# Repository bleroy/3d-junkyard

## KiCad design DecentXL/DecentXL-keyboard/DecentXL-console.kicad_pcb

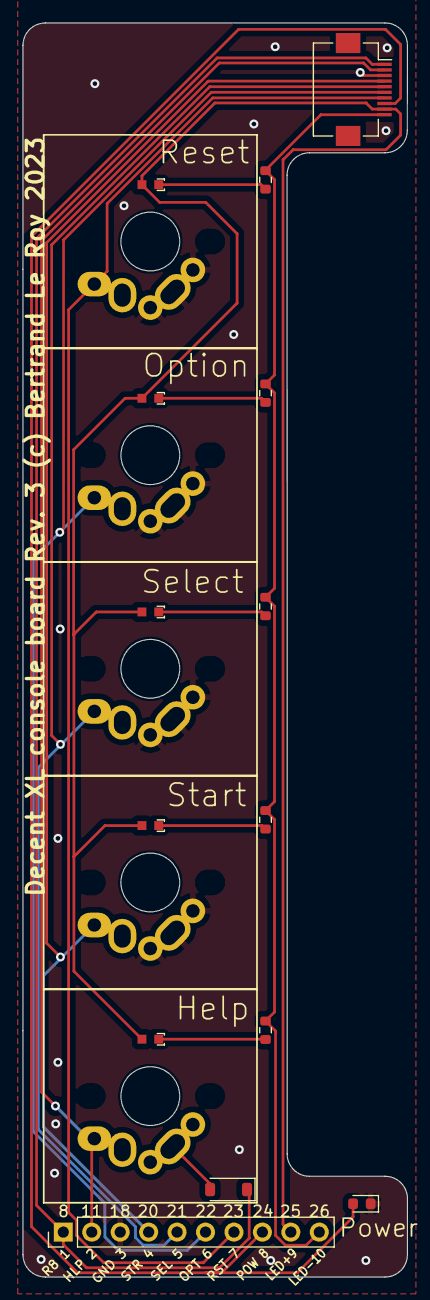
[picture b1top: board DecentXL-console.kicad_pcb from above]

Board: 2 copper layers, 34.3 x 112.0 mm, 14 parts (0 on the bottom side), 16 nets.

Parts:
D0: LED; LED_0603_1608Metric
D11: 1N4148W; D_SOD-123
J4: Conn_01x10; PinHeader_1x10_P2.54mm_Vertical
J5: Conn_01x10; Hirose_FH12-10S-0.5SH_1x10-1MP_P0.50mm_Horizontal
R11, R64, R65, R67, R68: 100; R_0603_1608Metric
SWHlp1: SW_Push_45deg; MX-1-00U-LED
SWOption1: SW_Push_45deg; MX-1-00U-LED
SWReset1: SW_Push_45deg; MX-1-00U-LED
SWSelect1: SW_Push_45deg; MX-1-00U-LED
SWStart1: SW_Push_45deg; MX-1-00U-LED

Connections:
CSL_GND: D0.1 (K), J4.3, J5.3, SWOption1.2, SWReset1.2, SWSelect1.2, SWStart1.2
CSL_HELP: J4.2, J5.2, SWHlp1.1
CSL_LED_GND: J4.10, J5.10, R11.2, R64.2, R65.2, R67.2, R68.2
CSL_OPTION: J4.6, J5.6, SWOption1.1
CSL_PWR_LED: D0.2 (A), J4.8, J5.8
CSL_RESET: J4.7, J5.7, SWReset1.1
CSL_ROW_8: D11.1 (K), J4.1, J5.1
CSL_SELECT: J4.5, J5.5, SWSelect1.1
CSL_START: J4.4, J5.4, SWStart1.1
CSL_VCC_LED: J4.9, J5.9, SWHlp1.4, SWOption1.4, SWReset1.4, SWSelect1.4, SWStart1.4
unnamed: D11.2 (A), SWHlp1.2
unnamed: R11.1, SWHlp1.3
unnamed: R64.1, SWStart1.3
unnamed: R65.1, SWSelect1.3
unnamed: R67.1, SWOption1.3
unnamed: R68.1, SWReset1.3

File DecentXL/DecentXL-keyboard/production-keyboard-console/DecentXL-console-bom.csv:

Designator,Footprint,Quantity,Value,LCSC Part #
D0,0603,1,LED,
D11,D_SOD-123,1,1N4148W,
J5,Hirose_FH12-10S-0.5SH_1x10-1MP_P0.50mm_Horizontal,1,Conn_01x10,
"R11, R64, R65, R67, R68",0603,5,100,
"SWHlp1, SWOption1, SWReset1, SWSelect1, SWStart1",MX-1-00U-LED,5,SW_Push_45deg,

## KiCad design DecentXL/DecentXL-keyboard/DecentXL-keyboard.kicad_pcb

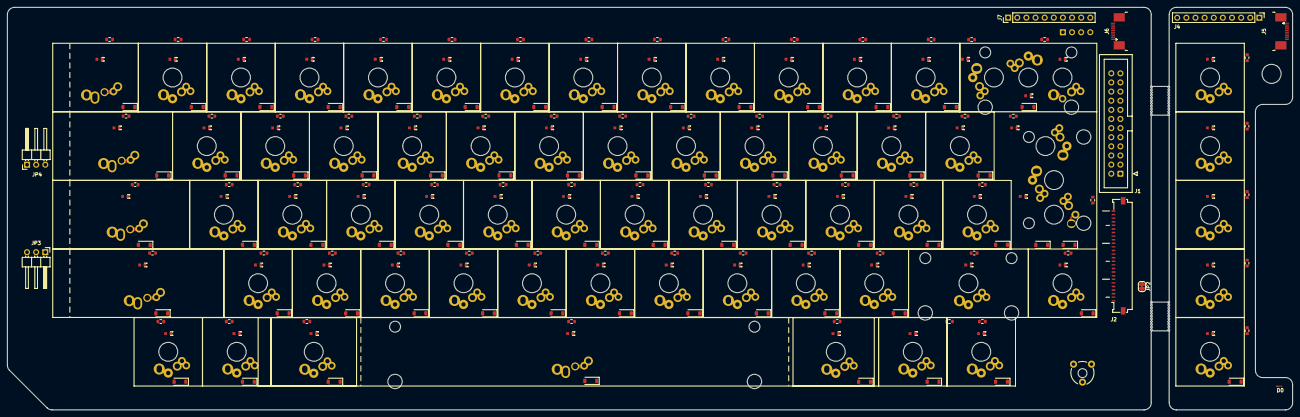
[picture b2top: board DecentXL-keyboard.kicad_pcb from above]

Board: 2 copper layers, 357.6 x 112.0 mm, 212 parts (1 on the bottom side), 168 nets, no tracks yet.

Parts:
D0: LED; LED_0201_0603Metric
D1, D2, D3, D4, D5, D6, D7, D8, D9, D10, D11, D12, D13, D14, D15, D16, D17, D18, D19, D20, D21, D22, D23, D24, D25, D26, D27, D28, D29, D30, D31, D32, D33, D34, D35, D36, D37, D38, D39, D40, D41, D42, D43, D44, D45, D46, D47, D48, D49, D50, D51, D52, D53, D54, D55, D56, D57, D58, D59, D60, D61, D62: 1N4148W; D_SOD-123
J1: Conn_02x12_Odd_Even; IDC-Header_2x12_P2.54mm_Vertical
J2: Conn_01x26; Molex_200528-0260_1x26-1MP_P1.00mm_Horizontal
J3: Conn_01x04; PinHeader_1x04_P2.54mm_Vertical
J4, J7: Conn_01x10; PinHeader_1x10_P2.54mm_Vertical
J5, J6: Conn_01x10; TE_1-1734839-0_1x10-1MP_P0.5mm_Horizontal
JP1: SolderJumper_2_Bridged; Potentiometer_CUI-PTN06-D02CB20
JP2: SolderJumper_2_Bridged; SolderJumper-2_P1.3mm_Bridged_RoundedPad1.0x1.5mm
JP3, JP4: Jumper_3_Bridged12; PinHeader_1x03_P2.54mm_Horizontal
R1, R2, R3, R4, R5, R6, R7, R8, R9, R10, R11, R12, R13, R14, R15, R16, R17, R18, R19, R20, R21, R22, R23, R24, R25, R26, R27, R28, R29, R30, R31, R32, R33, R34, R35, R36, R37, R38, R39, R40, R41, R42, R43, R44, R45, R46, R47, R48, R49, R50, R51, R52, R53, R54, R55, R56, R57, R58, R59, R60, R61, R62, R63, R64, R65, R66, R67, R68: R; R_0603_1608Metric
SW0, SW1, SW2, SW3, SW4, SW5, SW6, SW7, SW8, SW9: SW_Push_45deg; MX-1-00U-LED
SWA1: SW_Push_45deg; MX-1-00U-LED
SWB1: SW_Push_45deg; MX-1-00U-LED
SWBrk1: SW_Push_45deg; MX-1-25U-LED
SWBrk2: SW_Push_45deg; MX-1-00U-LED
SWC1: SW_Push_45deg; MX-1-00U-LED
SWComma1: SW_Push_45deg; MX-1-00U-LED
SWCps1: SW_Push_45deg; MX-1-25U-LED
SWCtl1: SW_Push_45deg; MX-1-25U-LED
SWCtlCaps1: SW_Push_45deg; MX-2-00--1-75-U-LED
SWD1: SW_Push_45deg; MX-1-00U-LED
SWDash1: SW_Push_45deg; MX-1-00U-LED
SWDel1: SWITCH; MX-2-00U-LED
SWDel2: SW_Push_45deg; MX-1-00U-LED
SWE1: SW_Push_45deg; MX-1-00U-LED
SWEqual1: SW_Push_45deg; MX-1-00U-LED
SWEsc1: SW_Push_45deg; MX-1-25--1-00-U-LED
SWF1: SW_Push_45deg; MX-1-00U-LED
SWFn1, SWFn2, SWFn3, SWFn4: SW_Push_45deg; MX-1-00U-LED
SWG1: SW_Push_45deg; MX-1-00U-LED
SWGT1: SW_Push_45deg; MX-1-00U-LED
SWH1: SW_Push_45deg; MX-1-00U-LED
SWHlp1: SW_Push_45deg; MX-1-00U-LED
SWI1: SW_Push_45deg; MX-1-00U-LED
SWInv1: SW_Push_45deg; MX-1-00U-LED
SWJ1: SW_Push_45deg; MX-1-00U-LED
SWK1: SW_Push_45deg; MX-1-00U-LED
SWL1: SW_Push_45deg; MX-1-00U-LED
SWLT1: SW_Push_45deg; MX-1-00U-LED
SWLeftSft1: SW_Push_45deg; MX-2-50U-LED
SWM1: SW_Push_45deg; MX-1-00U-LED
SWN1: SW_Push_45deg; MX-1-00U-LED
SWO1: SW_Push_45deg; MX-1-00U-LED
SWOption1: SW_Push_45deg; MX-1-00U-LED
SWP1: SW_Push_45deg; MX-1-00U-LED
SWPeriod1: SW_Push_45deg; MX-1-00U-LED
SWPlus1: SW_Push_45deg; MX-1-00U-LED
SWQ1: SW_Push_45deg; MX-1-00U-LED
SWR1: SW_Push_45deg; MX-1-00U-LED
SWReset1: SW_Push_45deg; MX-1-00U-LED
SWRet1: SWITCH; MX-ISO-RETURN
SWRet2: SW_Push_45deg; MX-1-50U-LED
SWRightSft1: SW_Push_45deg; MX-1-75U-LED
SWS1: SW_Push_45deg; MX-1-00U-LED
SWSelect1: SW_Push_45deg; MX-1-00U-LED
SWSemi1: SW_Push_45deg; MX-1-00U-LED
SWSlash1: SW_Push_45deg; MX-1-00U-LED
SWSpc1: SW_Push_45deg; MX-9-00--6-25-U-LED
SWStar1: SW_Push_45deg; MX-1-00U-LED
SWStart1: SW_Push_45deg; MX-1-00U-LED
SWT1: SW_Push_45deg; MX-1-00U-LED
SWTab1: SW_Push_45deg; MX-1-75--1-50-U-LED
SWU1: SW_Push_45deg; MX-1-00U-LED
SWV1: SW_Push_45deg; MX-1-00U-LED
SWW1: SW_Push_45deg; MX-1-00U-LED
SWX1: SW_Push_45deg; MX-1-00U-LED
SWY1: SW_Push_45deg; MX-1-00U-LED
SWZ1: SW_Push_45deg; MX-1-00U-LED

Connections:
COL_1: J1.9, J2.9, JP3.3 (B), SWBrk1.1, SWBrk2.1, SWCtl1.1, SWLeftSft1.1, SWRightSft1.1
COL_2: J1.10, J2.10, J3.1, SW6.1, SW7.1, SWFn1.1, SWFn3.1, SWN1.1, SWU1.1, SWY1.1
COL_3: J1.11, J2.11, J6.9, J7.9, SWH1.1, SWJ1.1, SWSpc1.1
COL_4: J1.12, J2.12, SW5.1, SW8.1, SWB1.1, SWG1.1, SWI1.1, SWK1.1, SWM1.1, SWT1.1
COL_5: J1.13, J2.13, SW4.1, SW9.1, SWComma1.1, SWF1.1, SWL1.1, SWO1.1, SWR1.1, SWV1.1
COL_6: J1.14, J2.14, SW0.1, SW3.1, SWC1.1, SWD1.1, SWE1.1, SWP1.1, SWPeriod1.1, SWSemi1.1
COL_7: J1.15, J2.15, SW2.1, SWDash1.1, SWLT1.1, SWPlus1.1, SWS1.1, SWSlash1.1, SWW1.1, SWX1.1
COL_8: J1.16, J2.16, SW1.1, SWA1.1, SWEqual1.1, SWGT1.1, SWInv1.1, SWQ1.1, SWStar1.1, SWZ1.1
COL_9: J1.17, J2.17, J3.2, JP3.1 (A), SWCps1.1, SWDel1.1, SWDel2.1, SWEsc1.1, SWFn2.1, SWFn4.1, SWRet1.1, SWRet2.1, SWTab1.1
CSL_GND: D0.1 (K), J4.3, J5.3, SWOption1.2, SWReset1.2, SWSelect1.2, SWStart1.2
CSL_HELP: J4.2, J5.2, SWHlp1.1
CSL_LED_GND: J4.10, J5.10, R11.2, R64.2, R65.2, R67.2, R68.2
CSL_OPTION: J4.6, J5.6, SWOption1.1
CSL_PWR_LED: D0.2 (A), J4.8, J5.8
CSL_RESET: J4.7, J5.7, SWReset1.1
CSL_ROW_8: D11.1 (K), J4.1, J5.1
CSL_SELECT: J4.5, J5.5, SWSelect1.1
CSL_START: J4.4, J5.4, SWStart1.1
CSL_VCC_LED: J4.9, J5.9, SWHlp1.4, SWOption1.4, SWReset1.4, SWSelect1.4, SWStart1.4
GND: J1.18, J2.18, J6.8, J7.8, JP2.1 (A)
LED_GND: J2.26, J6.1, J7.1, JP2.2 (B), R1.2, R2.2, R3.2, R4.2, R5.2, R6.2, R7.2, R8.2, R9.2, R10.2, R12.2, R13.2, R14.2, R15.2, R16.2, R17.2, R18.2, R19.2, R20.2, R21.2, R22.2, R23.2, R24.2, R25.2, R26.2, R27.2, R28.2, R29.2, R30.2, R31.2, R32.2, R33.2, R34.2, R35.2, R36.2, R37.2, R38.2, R39.2, R40.2, R41.2, R42.2, R43.2, R44.2, R45.2, R46.2, R47.2, R48.2, R49.2, R50.2, R51.2, R52.2, R53.2, R54.2, R55.2, R56.2, R57.2, R58.2, R59.2, R60.2, R61.2, R62.2, R63.2, R66.2
unnamed: D1.2 (A), SW7.2
unnamed: D2.2 (A), SW6.2
unnamed: D3.2 (A), SWU1.2
unnamed: D4.2 (A), SWY1.2
unnamed: D5.2 (A), SWFn1.2
unnamed: D6.2 (A), SWN1.2
unnamed: D7.2 (A), SWFn3.2
unnamed: D8.2 (A), SWJ1.2
unnamed: D9.2 (A), SWH1.2
unnamed: D10.2 (A), SWSpc1.2
unnamed: D11.2 (A), SWHlp1.2
unnamed: D12.2 (A), SW8.2
unnamed: D13.2 (A), SW5.2
unnamed: D14.2 (A), SWI1.2
unnamed: D15.2 (A), SWT1.2
unnamed: D16.2 (A), SWK1.2
unnamed: D17.2 (A), SWG1.2
unnamed: D18.2 (A), SWM1.2
unnamed: D19.2 (A), SWB1.2
unnamed: D20.2 (A), SW9.2
unnamed: D21.2 (A), SW4.2
unnamed: D22.2 (A), SWO1.2
unnamed: D23.2 (A), SWR1.2
unnamed: D24.2 (A), SWL1.2
unnamed: D25.2 (A), SWF1.2
unnamed: D26.2 (A), SWComma1.2
unnamed: D27.2 (A), SWV1.2
unnamed: D28.2 (A), SW0.2
unnamed: D29.2 (A), SW3.2
unnamed: D30.2 (A), SWP1.2
unnamed: D31.2 (A), SWE1.2
unnamed: D32.2 (A), SWSemi1.2
unnamed: D33.2 (A), SWD1.2
unnamed: D34.2 (A), SWPeriod1.2
unnamed: D35.2 (A), SWC1.2
unnamed: D36.2 (A), SWLT1.2
unnamed: D37.2 (A), SW2.2
unnamed: D38.2 (A), SWDash1.2
unnamed: D39.2 (A), SWW1.2
unnamed: D40.2 (A), SWPlus1.2
unnamed: D41.2 (A), SWS1.2
unnamed: D42.2 (A), SWSlash1.2
unnamed: D43.2 (A), SWX1.2
unnamed: D44.2 (A), SWGT1.2
unnamed: D45.2 (A), SW1.2
unnamed: D46.2 (A), SWEqual1.2
unnamed: D47.2 (A), SWQ1.2
unnamed: D48.2 (A), SWStar1.2
unnamed: D49.2 (A), SWA1.2
unnamed: D50.2 (A), SWInv1.2
unnamed: D51.2 (A), SWZ1.2
unnamed: D52.2 (A), SWDel1.2, SWDel2.2
unnamed: D53.2 (A), SWEsc1.2
unnamed: D54.2 (A), SWRet1.2, SWRet2.2
unnamed: D55.2 (A), SWTab1.2
unnamed: D56.2 (A), SWFn2.2
unnamed: D57.2 (A), SWCps1.2
unnamed: D58.2 (A), SWFn4.2
unnamed: D59.2 (A), SWBrk1.2, SWBrk2.2
unnamed: D60.2 (A), SWCtl1.2
unnamed: D61.2 (A), SWLeftSft1.2, SWRightSft1.2
unnamed: D62.2 (A), SWCtlCaps1.2
unnamed: D62.1 (K), JP4.2 (C)
unnamed: JP3.2 (C), SWCtlCaps1.1
unnamed: R1.1, SW7.3
unnamed: R2.1, SW6.3
unnamed: R3.1, SWU1.3
unnamed: R4.1, SWY1.3
unnamed: R5.1, SWFn1.3
unnamed: R6.1, SWN1.3
unnamed: R7.1, SWFn3.3
unnamed: R8.1, SWJ1.3
unnamed: R9.1, SWH1.3
unnamed: R10.1, SWSpc1.3
unnamed: R11.1, SWHlp1.3
unnamed: R12.1, SW8.3
unnamed: R13.1, SW5.3
unnamed: R14.1, SWI1.3
unnamed: R15.1, SWT1.3
unnamed: R16.1, SWK1.3
unnamed: R17.1, SWG1.3
unnamed: R18.1, SWM1.3
unnamed: R19.1, SWB1.3
unnamed: R20.1, SW9.3
unnamed: R21.1, SW4.3
unnamed: R22.1, SWO1.3
unnamed: R23.1, SWR1.3
unnamed: R24.1, SWL1.3
unnamed: R25.1, SWF1.3
unnamed: R26.1, SWComma1.3
unnamed: R27.1, SWV1.3
unnamed: R28.1, SW0.3
unnamed: R29.1, SW3.3
unnamed: R30.1, SWP1.3
unnamed: R31.1, SWE1.3
unnamed: R32.1, SWSemi1.3
unnamed: R33.1, SWD1.3
unnamed: R34.1, SWPeriod1.3
unnamed: R35.1, SWC1.3
unnamed: R36.1, SWLT1.3
unnamed: R37.1, SW2.3
unnamed: R38.1, SWDash1.3
unnamed: R39.1, SWW1.3
unnamed: R40.1, SWPlus1.3
unnamed: R41.1, SWS1.3
unnamed: R42.1, SWSlash1.3
unnamed: R43.1, SWX1.3
unnamed: R44.1, SWGT1.3
unnamed: R45.1, SW1.3
unnamed: R46.1, SWEqual1.3
unnamed: R47.1, SWQ1.3
unnamed: R48.1, SWStar1.3
unnamed: R49.1, SWA1.3
unnamed: R50.1, SWInv1.3
unnamed: R51.1, SWZ1.3
unnamed: R52.1, SWEsc1.3
unnamed: R53.1, SWDel2.3
unnamed: R54.1, SWRet2.3
unnamed: R55.1, SWTab1.3
unnamed: R56.1, SWFn2.3
unnamed: R57.1, SWCps1.3
unnamed: R58.1, SWFn4.3
unnamed: R59.1, SWBrk1.3
unnamed: R60.1, SWCtl1.3
unnamed: R61.1, SWRightSft1.3
unnamed: R62.1, SWBrk2.3
unnamed: R63.1, SWLeftSft1.3
unnamed: R64.1, SWStart1.3
unnamed: R65.1, SWSelect1.3
unnamed: R66.1, SWCtlCaps1.3
unnamed: R67.1, SWOption1.3
unnamed: R68.1, SWReset1.3
OPTION: J1.22, J2.22, J6.5, J7.5
POWER: J1.19, J2.19, JP1.1 (A)
PWR_LED: J1.24, J2.24, J6.3, J7.3
RESET: J1.23, J2.23, J6.4, J7.4
ROW_1: D1.1 (K), D12.1 (K), D20.1 (K), D28.1 (K), D36.1 (K), D44.1 (K), D52.1 (K), D59.1 (K), J1.1, J2.1
ROW_2: D2.1 (K), D13.1 (K), D21.1 (K), D29.1 (K), D37.1 (K), D45.1 (K), D53.1 (K), J1.2, J2.2
ROW_3: D3.1 (K), D14.1 (K), D22.1 (K), D30.1 (K), D38.1 (K), D46.1 (K), D54.1 (K), J1.3, J2.3
ROW_4: D4.1 (K), D15.1 (K), D23.1 (K), D31.1 (K), D39.1 (K), D47.1 (K), D55.1 (K), J1.4, J2.4
ROW_5: D5.1 (K), D8.1 (K), D16.1 (K), D24.1 (K), D32.1 (K), D40.1 (K), D48.1 (K), D56.1 (K), D60.1 (K), J1.5, J2.5, J3.3, JP4.1 (A)
ROW_6: D9.1 (K), D17.1 (K), D25.1 (K), D33.1 (K), D41.1 (K), D49.1 (K), D57.1 (K), J1.6, J2.6, JP4.3 (B)
ROW_7: D6.1 (K), D10.1 (K), D18.1 (K), D26.1 (K), D34.1 (K), D42.1 (K), D50.1 (K), J1.7, J2.7
ROW_8: D7.1 (K), D19.1 (K), D27.1 (K), D35.1 (K), D43.1 (K), D51.1 (K), D58.1 (K), D61.1 (K), J1.8, J2.8, J3.4, J6.10, J7.10
SELECT: J1.21, J2.21, J6.6, J7.6
START: J1.20, J2.20, J6.7, J7.7
VCC_LED: J2.25, J6.2, J7.2, JP1.2 (B), SW0.4, SW1.4, SW2.4, SW3.4, SW4.4, SW5.4, SW6.4, SW7.4, SW8.4, SW9.4, SWA1.4, SWB1.4, SWBrk1.4, SWBrk2.4, SWC1.4, SWComma1.4, SWCps1.4, SWCtl1.4, SWCtlCaps1.4, SWD1.4, SWDash1.4, SWDel2.4, SWE1.4, SWEqual1.4, SWEsc1.4, SWF1.4, SWFn1.4, SWFn2.4, SWFn3.4, SWFn4.4, SWG1.4, SWGT1.4, SWH1.4, SWI1.4, SWInv1.4, SWJ1.4, SWK1.4, SWL1.4, SWLT1.4, SWLeftSft1.4, SWM1.4, SWN1.4, SWO1.4, SWP1.4, SWPeriod1.4, SWPlus1.4, SWQ1.4, SWR1.4, SWRet2.4, SWRightSft1.4, SWS1.4, SWSemi1.4, SWSlash1.4, SWSpc1.4, SWStar1.4, SWT1.4, SWTab1.4, SWU1.4, SWV1.4, SWW1.4, SWX1.4, SWY1.4, SWZ1.4

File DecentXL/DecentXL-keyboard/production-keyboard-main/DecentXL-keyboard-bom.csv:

Designator,Footprint,Quantity,Value,LCSC Part #
"D1, D10, D12, D13, D14, D15, D16, D17, D18, D19, D2, D20, D21, D22, D23, D24, D25, D26, D27, D28, D29, D3, D30, D31, D32, D33, D34, D35, D36, D37, D38, D39, D4, D40, D41, D42, D43, D44, D45, D46, D47, D48, D49, D5, D50, D51, D52, D53, D54, D55, D56, D57, D58, D59, D6, D60, D61, D62, D7, D8, D9",D_SOD-123,61,1N4148W,C81598
J2,Molex_200528-0260_1x26-1MP_P1.00mm_Horizontal,1,Conn_01x26,C60248
J6,Hirose_FH12-10S-0.5SH_1x10-1MP_P0.50mm_Horizontal,1,Conn_01x10,C709365
"R1, R10, R12, R13, R14, R15, R16, R17, R18, R19, R2, R20, R21, R22, R23, R24, R25, R26, R27, R28, R29, R3, R30, R31, R32, R33, R34, R35, R36, R37, R38, R39, R4, R40, R41, R42, R43, R44, R45, R46, R47, R48, R49, R5, R50, R51, R52, R53, R54, R55, R56, R57, R58, R59, R6, R60, R61, R62, R63, R66, R7, R8, R9",0603,63,100,C22775
RV1,Potentiometer_Bourns_TC33X_Vertical,1,Potentiometer,
SW0,MX-1-00U-LED,1,0,C193191
SW1,MX-1-00U-LED,1,1,C193191
SW2,MX-1-00U-LED,1,2,C193191
SW3,MX-1-00U-LED,1,3,C193191
SW4,MX-1-00U-LED,1,4,C193191
SW5,MX-1-00U-LED,1,5,C193191
SW6,MX-1-00U-LED,1,6,C193191
SW7,MX-1-00U-LED,1,7,C193191
SW8,MX-1-00U-LED,1,8,C193191
SW9,MX-1-00U-LED,1,9,C193191
SWA1,MX-1-00U-LED,1,A,C193191
SWB1,MX-1-00U-LED,1,B,C193191
SWBrk1,MX-1-25U-LED,1,Break,C193191
SWBrk2,Choc-Alps-1-00U-LED,1,Break,C193191
SWC1,MX-1-00U-LED,1,C,C193191
SWComma1,MX-1-00U-LED,1,Comma,C193191
SWCps1,Choc-Alps-1-25U-LED,1,Caps,C193191
SWCtl1,MX-1-25U-LED,1,Control,C193191
SWCtlCaps1,MX-2-00--1-75-U-LED,1,Caps,C193191
SWD1,MX-1-00U-LED,1,D,C193191
SWDash1,MX-1-00U-LED,1,Dash,C193191
SWDel2,MX-1-00U-LED,1,Del,C193191
SWE1,MX-1-00U-LED,1,E,C193191
SWEqual1,MX-1-00U-LED,1,Equal,C193191
SWEsc1,MX-1-25--1-00-U-LED,1,Esc,C193191
SWF1,MX-1-00U-LED,1,F,C193191
SWFn1,MX-1-00U-LED,1,F1,C193191
SWFn2,MX-1-00U-LED,1,F2,C193191
SWFn3,MX-1-00U-LED,1,F3,C193191
SWFn4,MX-1-00U-LED,1,F4,C193191
SWG1,MX-1-00U-LED,1,G,C193191
SWGT1,MX-1-00U-LED,1,GreaterThan,C193191
SWH1,MX-1-00U-LED,1,H,C193191
SWI1,MX-1-00U-LED,1,I,C193191
SWInv1,MX-1-00U-LED,1,Inverse,C193191
SWJ1,MX-1-00U-LED,1,J,C193191
SWK1,MX-1-00U-LED,1,K,C193191
SWL1,MX-1-00U-LED,1,L,C193191
SWLT1,MX-1-00U-LED,1,LessThan,C193191
SWLeftSft1,MX-2-50--2-25-U-LED,1,Shift,C193191
SWM1,MX-1-00U-LED,1,M,C193191
SWN1,MX-1-00U-LED,1,N,C193191
SWO1,MX-1-00U-LED,1,O,C193191
SWP1,MX-1-00U-LED,1,P,C193191
SWPeriod1,MX-1-00U-LED,1,Period,C193191
SWPlus1,MX-1-00U-LED,1,Plus,C193191
SWQ1,MX-1-00U-LED,1,Q,C193191
SWR1,MX-1-00U-LED,1,R,C193191
SWRet2,Choc-Alps-1-50U-LED,1,Return,C193191
SWRightSft1,MX-1-75U-LED,1,Shift,C193191
SWS1,MX-1-00U-LED,1,S,C193191
SWSemi1,MX-1-00U-LED,1,Semicolon,C193191
SWSlash1,MX-1-00U-LED,1,Slash,C193191
SWSpc1,MX-9-00--6-25-U-LED,1,Space,C193191
SWStar1,MX-1-00U-LED,1,Star,C193191
SWT1,MX-1-00U-LED,1,T,C193191
SWTab1,MX-1-75--1-50-U-LED,1,Tab,C193191
SWU1,MX-1-00U-LED,1,U,C193191
SWV1,MX-1-00U-LED,1,V,C193191
SWW1,MX-1-00U-LED,1,W,C193191
SWX1,MX-1-00U-LED,1,X,C193191
SWY1,MX-1-00U-LED,1,Y,C193191
SWZ1,MX-1-00U-LED,1,Z,C193191

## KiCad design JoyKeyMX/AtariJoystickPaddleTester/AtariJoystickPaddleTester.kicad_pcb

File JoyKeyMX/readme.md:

# JoyKey - an Atari-compatible joystick built with mechanical switches

## JoyKey Mini vs. JoyKey XL

There are two models of JoyKey: JoyKey Mini and JoyKey XL.

The Mini is a small and simple four directions and fire controller with a 9-pin Atari-compatible plug. It's designed with Atari 8-bit computers and consoles in mind, but it can be used with any compatible retro systemm such as the C64.

The XL is designed to maximize the potential of the Atari 8-bit joystick port.
It has the same four directions and fire as the Mini, but adds two fire buttons using the Atari 7800 wiring and two analog paddles.

## Configuration

The Mini has no configuration, just plug and play. The XL has a single switch in the back to choose to use the paddles or the two additional fire buttons.
In paddle mode, the additional fires act as the regular fire button.

### LED configuration

The LED circuit is using the 5V from pin 7 and ground from pin 8 by default.
If the device you're connecting the JoyKey to doesn't have 5V on pin 7, or if you want to externally provide power, you can choose to not connect those pins on the JoyKey and instead privide power through the J3 LED power connector.

## Schematic

### JoyKey Mini

### JoyKey XL

## Fabrication

* [JoyKey Mini Gerber files](Fabrication/JoyKeyMini.zip)
* [JoyKey Mini BOM](Fabrication/JoyKeyMini-BOM.csv)
* [JoyKey Mini Positions](Fabrication/JoyKeyMini-all-pos.csv)
* [JoyKey Mini Enclosure bottom part](Case/JoyKeyMiniCase-Bottom.stl)
* [JoyKey Mini Enclosure top part](Case/JoyKeyMiniCase-Top.stl)
* [JoyKey XL Gerber files](Fabrication/JoyKeyXL.zip)
* [JoyKey XL BOM](Fabrication/JoyKeyMX-BOM.csv)
* [JoyKey XL Positions](Fabrication/JoyKeyMX-top-pos.csv)
* [JoyKey XL Al plate Gerber files](Fabrication/JoyKeyMX-plate.zip)
* [JoyKey XL Enclosure bottom part](Case/JoyKeyMiniCase-Bottom.stl)
* [JoyKey XL Enclosure top part](Case/JoyKeyMiniCase-Top.stl)

## License

All hardware in this repository is licensed under [CERN Open Hardware License v2](https://ohwr.org/cern_ohl_p_v2.pdf).
All software in this repository is licensed under the [MIT license](https://mit-license.org/).
All documentation in this repository is licensed under [Creative Commons Creative Commons Attribution-ShareAlike 4.0 International Public License](https://creativecommons.org/licenses/by-sa/4.0/legalcode).

Full terms can be found in the [LICENSE](./LICENSE) file or on the web sites linked above.

## OSHW certification

This project is [certified open source hardware by OSHWA](https://certification.oshwa.org/us002379.html).

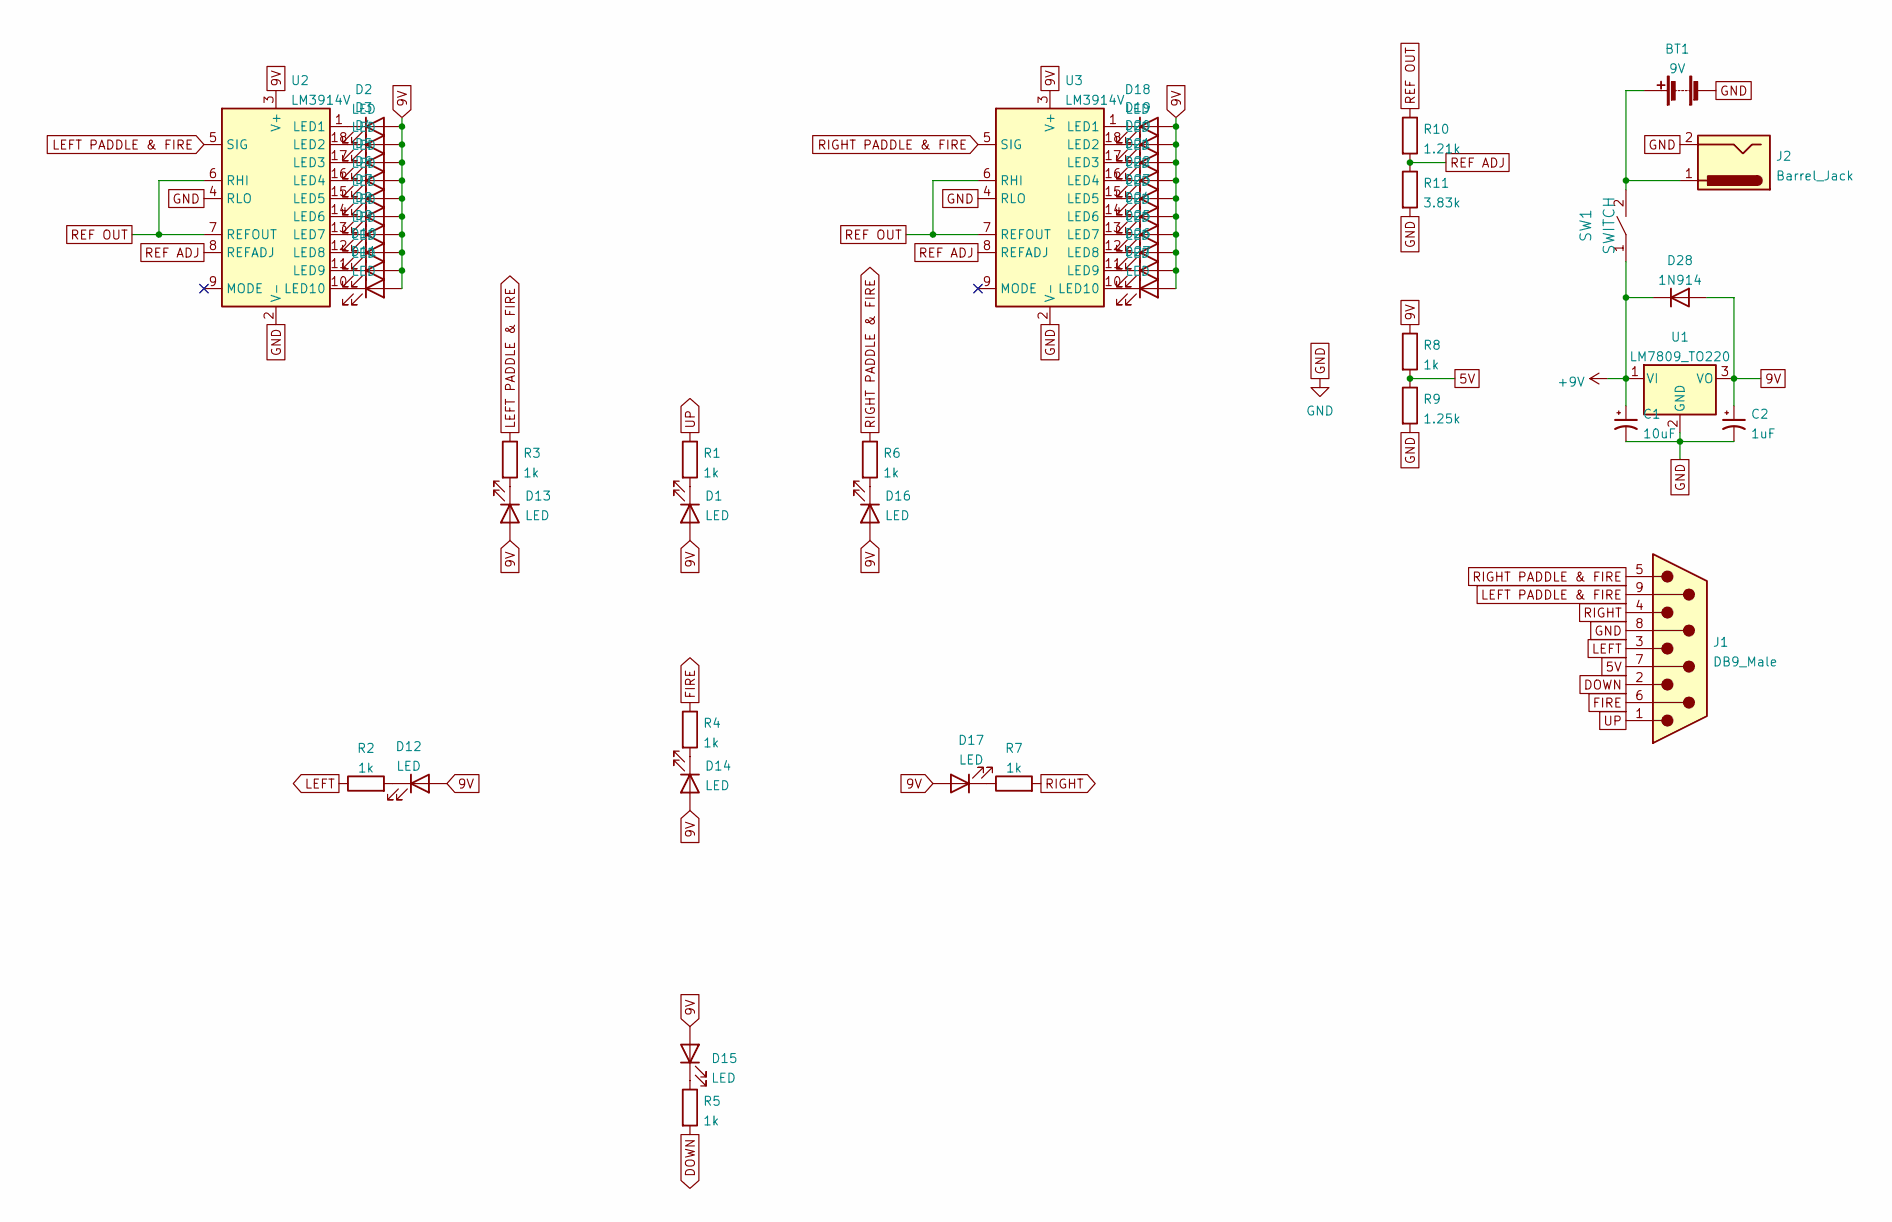
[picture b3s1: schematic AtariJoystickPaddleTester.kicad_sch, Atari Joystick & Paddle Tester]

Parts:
BT1: 9V; BatteryHolder_MPD_BA9VPC_1xPP3
C1: 10uF; CP_Radial_D5.0mm_P2.50mm
C2: 1uF; CP_Radial_D5.0mm_P2.50mm
D1, D2, D3, D4, D5, D6, D7, D8, D9, D10, D11, D12, D13, D14, D15, D16, D17, D18, D19, D20, D21, D22, D23, D24, D25, D26, D27: LED; LED_D10.0mm
D28: 1N914; D_DO-35_SOD27_P7.62mm_Horizontal
J1: DB9_Male; DSUB-9_Male_Horizontal_P2.77x2.84mm_EdgePinOffset4.94mm_Hou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
J2: Barrel_Jack; BarrelJack_Horizontal
R1, R2, R3, R4, R5, R6, R7, R8: 1k; R_Axial_DIN0207_L6.3mm_D2.5mm_P7.62mm_Horizontal
R9: 1.25k; R_Axial_DIN0207_L6.3mm_D2.5mm_P7.62mm_Horizontal
R10: 1.21k; R_Axial_DIN0207_L6.3mm_D2.5mm_P7.62mm_Horizontal
R11: 3.83k; R_Axial_DIN0207_L6.3mm_D2.5mm_P7.62mm_Horizontal
SW1: SWITCH; Slide Switch 3-pin
U1: LM7809_TO220; TO-220-3_Horizontal_TabDown
U2, U3: LM3914V; DIP-18_W7.62mm

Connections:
5V: J1.7, R8.2, R9.1
9V: C2.1, D1.2 (A), D2.2 (A), D3.2 (A), D4.2 (A), D5.2 (A), D6.2 (A), D7.2 (A), D8.2 (A), D9.2 (A), D10.2 (A), D11.2 (A), D12.2 (A), D13.2 (A), D14.2 (A), D15.2 (A), D16.2 (A), D17.2 (A), D18.2 (A), D19.2 (A), D20.2 (A), D21.2 (A), D22.2 (A), D23.2 (A), D24.2 (A), D25.2 (A), D26.2 (A), D27.2 (A), D28.2 (A), R8.1, U1.3 (VO), U2.3 (V+), U3.3 (V+)
+9V: C1.1, D28.1 (K), SW1.1, U1.1 (VI)
DOWN: J1.2, R5.2
FIRE: J1.6, R4.1
GND: BT1.2 (-), C1.2, C2.2, J1.8, J2.2, R9.2, R11.2, U1.2 (GND), U2.2 (V-), U2.4 (RLO), U3.2 (V-), U3.4 (RLO)
LEFT: J1.3, R2.1
LEFT PADDLE & FIRE: J1.9, R3.1, U2.5 (SIG)
unnamed: BT1.1 (+), J2.1, SW1.2
unnamed: D1.1 (K), R1.2
unnamed: D2.1 (K), U2.1 (LED1)
unnamed: D3.1 (K), U2.18 (LED2)
unnamed: D4.1 (K), U2.17 (LED3)
unnamed: D5.1 (K), U2.16 (LED4)
unnamed: D6.1 (K), U2.15 (LED5)
unnamed: D7.1 (K), U2.14 (LED6)
unnamed: D8.1 (K), U2.13 (LED7)
unnamed: D9.1 (K), U2.12 (LED8)
unnamed: D10.1 (K), U2.11 (LED9)
unnamed: D11.1 (K), U2.10 (LED10)
unnamed: D12.1 (K), R2.2
unnamed: D13.1 (K), R3.2
unnamed: D14.1 (K), R4.2
unnamed: D15.1 (K), R5.1
unnamed: D16.1 (K), R6.2
unnamed: D17.1 (K), R7.1
unnamed: D18.1 (K), U3.1 (LED1)
unnamed: D19.1 (K), U3.18 (LED2)
unnamed: D20.1 (K), U3.17 (LED3)
unnamed: D21.1 (K), U3.16 (LED4)
unnamed: D22.1 (K), U3.15 (LED5)
unnamed: D23.1 (K), U3.14 (LED6)
unnamed: D24.1 (K), U3.13 (LED7)
unnamed: D25.1 (K), U3.12 (LED8)
unnamed: D26.1 (K), U3.11 (LED9)
unnamed: D27.1 (K), U3.10 (LED10)
REF ADJ: R10.2, R11.1, U2.8 (REFADJ), U3.8 (REFADJ)
REF OUT: R10.1, U2.6 (RHI), U2.7 (REFOUT), U3.6 (RHI), U3.7 (REFOUT)
RIGHT: J1.4, R7.2
RIGHT PADDLE & FIRE: J1.5, R6.1, U3.5 (SIG)
UP: J1.1, R1.1

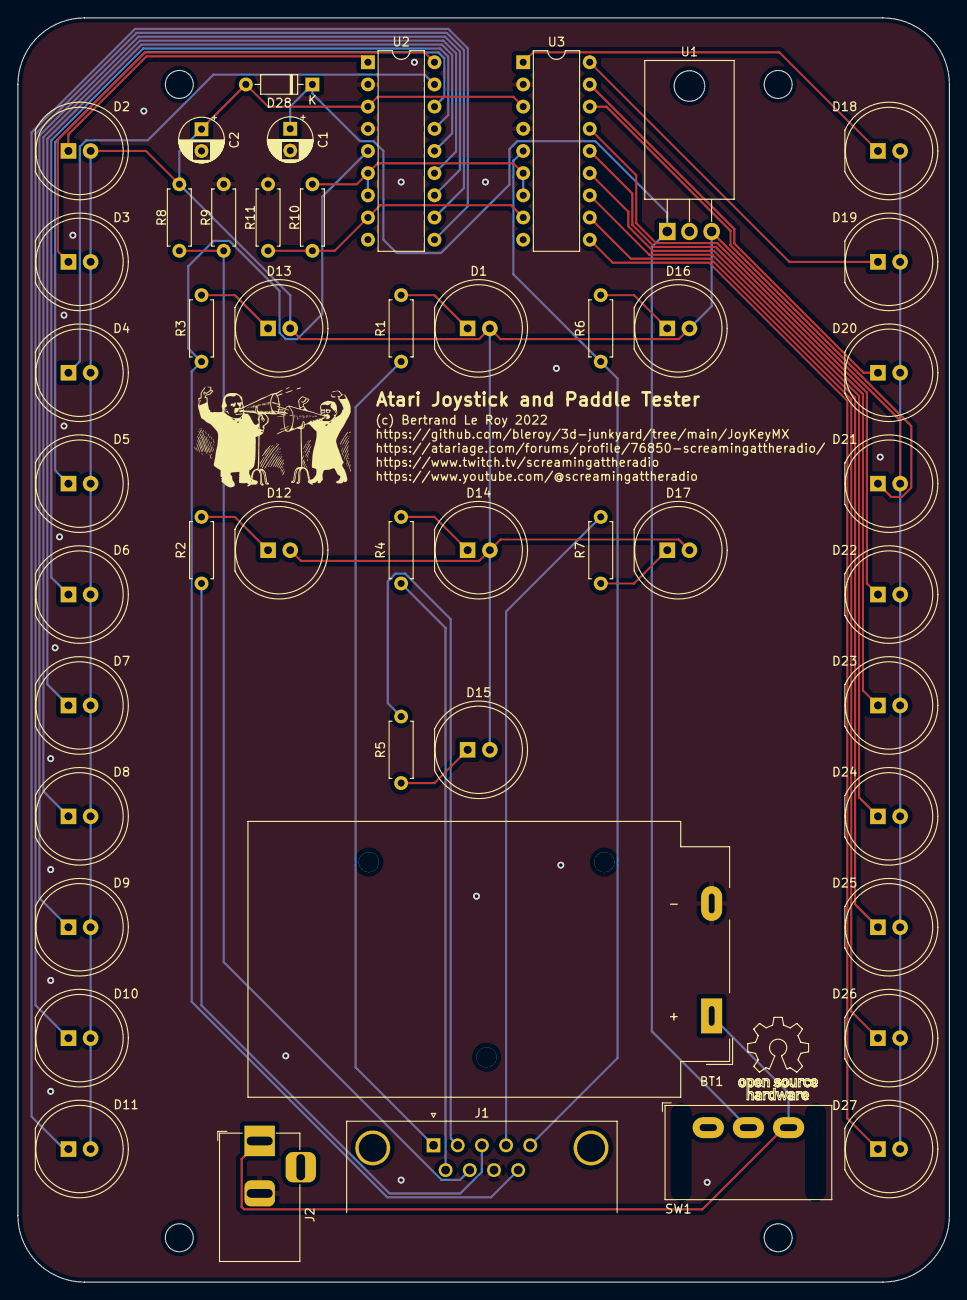
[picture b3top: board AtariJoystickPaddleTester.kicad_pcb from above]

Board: 2 copper layers, 106.7 x 144.8 mm, 48 parts (0 on the bottom side), 41 nets.

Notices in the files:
JoyKeyMX/readme.md:
Open source licenses
